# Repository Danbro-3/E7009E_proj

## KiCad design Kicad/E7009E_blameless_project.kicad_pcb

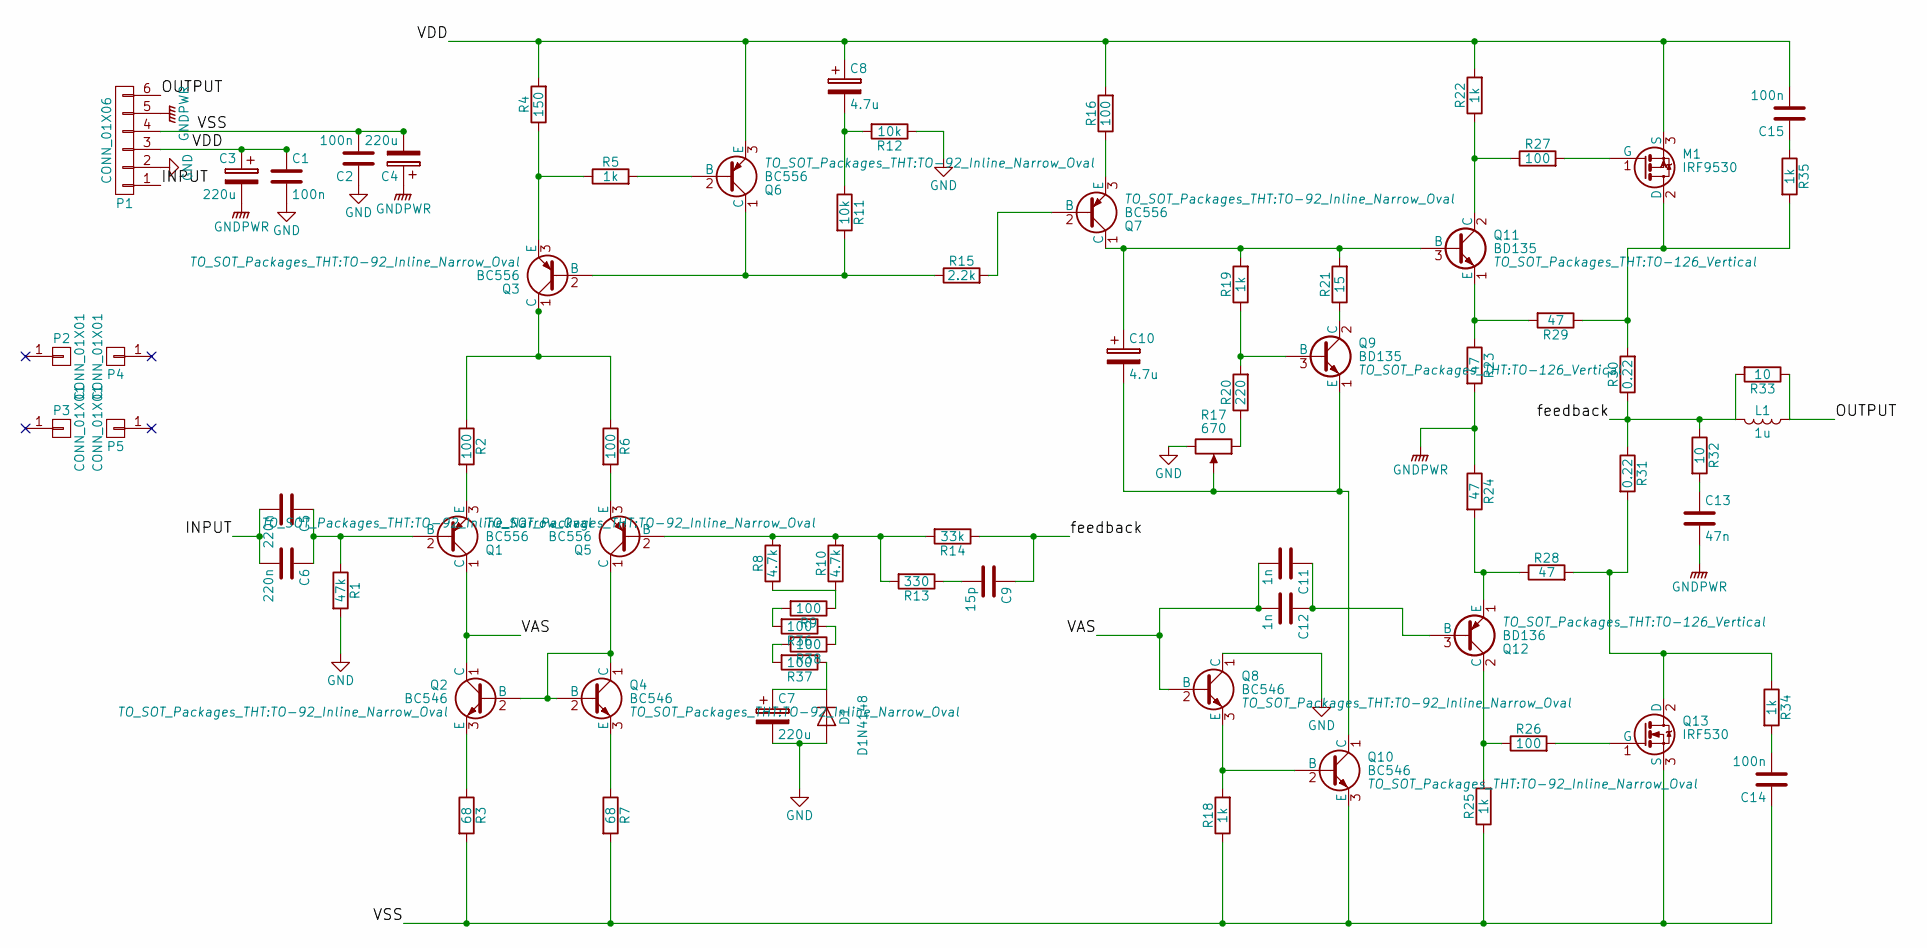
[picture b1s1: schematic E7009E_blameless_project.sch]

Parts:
C1, C2, C14, C15: 100n; C_Disc_D3.0mm_W2.0mm_P2.50mm
C3, C4, C7: 220u; CP_Radial_D8.0mm_P5.00mm
C5, C6: 220n; C_Disc_D3.0mm_W2.0mm_P2.50mm
C8, C10: 4.7u; CP_Radial_D5.0mm_P2.50mm
C9: 15p; C_Disc_D3.0mm_W1.6mm_P2.50mm
C11, C12: 1n; C_Disc_D3.0mm_W1.6mm_P2.50mm
C13: 47n; C_Disc_D3.0mm_W2.0mm_P2.50mm
D1: D1N4148; D_5W_P5.08mm_Vertical_AnodeUp
L1: 1u; Coil_p11mm_L15mm_d10mm
M1: IRF9530; TO-220_Vertical
P1: CONN_01X06; Pin_Header_Straight_1x06_Pitch2.54mm
P2, P3, P4, P5: CONN_01X01; Mounting_D3mm_Pad1mm_totd6mm
Q1, Q3, Q5, Q6, Q7: BC556; TO-92_Inline_Narrow_Oval
Q2, Q4, Q8, Q10: BC546; TO-92_Inline_Narrow_Oval
Q9, Q11: BD135; TO-126_Vertical
Q12: BD136; TO-126_Vertical
Q13: IRF530; TO-220_Vertical
R1: 47k; R_Axial_DIN0204_L3.6mm_D1.6mm_P5.08mm_Horizontal
R2, R6, R9, R16, R26, R27, R36, R37, R38: 100; R_Axial_DIN0204_L3.6mm_D1.6mm_P5.08mm_Horizontal
R3, R7: 68; R_Axial_DIN0204_L3.6mm_D1.6mm_P5.08mm_Horizontal
R4: 150; R_Axial_DIN0204_L3.6mm_D1.6mm_P5.08mm_Horizontal
R5, R18, R19, R22, R25, R34, R35: 1k; R_Axial_DIN0204_L3.6mm_D1.6mm_P5.08mm_Horizontal
R8, R10: 4.7k; R_Axial_DIN0204_L3.6mm_D1.6mm_P5.08mm_Horizontal
R11, R12: 10k; R_Axial_DIN0204_L3.6mm_D1.6mm_P5.08mm_Horizontal
R13: 330; R_Axial_DIN0204_L3.6mm_D1.6mm_P5.08mm_Horizontal
R14: 33k; R_Axial_DIN0204_L3.6mm_D1.6mm_P5.08mm_Horizontal
R15: 2.2k; R_Axial_DIN0204_L3.6mm_D1.6mm_P5.08mm_Horizontal
R17: 670; Potentiometer_Trimmer_Bourns_3296W
R20: 220; R_Axial_DIN0204_L3.6mm_D1.6mm_P5.08mm_Horizontal
R21: 15; R_Axial_DIN0204_L3.6mm_D1.6mm_P5.08mm_Horizontal
R23, R24, R28, R29: 47; R_Axial_DIN0204_L3.6mm_D1.6mm_P5.08mm_Horizontal
R30, R31: 0.22; R_Axial_DIN0207_L6.3mm_D2.5mm_P17.15mm_Horizontal
R32, R33: 10; R_Axial_DIN0414_L11.9mm_D4.5mm_P25.40mm_Horizontal

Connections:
/INPUT: C5.2, C6.2, P1.1
/OUTPUT: L1.1, P1.6, R33.1
/VAS: C11.2, C12.2, Q1.1 (C), Q2.1 (C), Q8.2 (B)
/VDD: C1.1, C3.1, C8.1, C15.2, M1.3 (S), P1.3, Q6.3 (E), R4.2, R16.2, R22.2
/VSS: C2.2, C4.2, C14.1, P1.4, Q10.3 (E), Q13.3 (S), R3.2, R7.2, R18.1, R25.1
/feedback: C9.1, L1.2, R14.1, R30.1, R31.1, R32.1, R33.2
GND: C1.2, C2.1, C7.2, D1.2 (A), P1.2, Q8.1 (C), R1.2, R12.1, R17.3
GNDPWR: C3.2, C4.1, C13.2, P1.5, R23.2, R24.1
unnamed: C5.1, C6.1, Q1.2 (B), R1.1
unnamed: C7.1, D1.1 (K), R37.1
unnamed: C8.2, R11.1, R12.2
unnamed: C9.2, R13.1
unnamed: C10.1, Q7.1 (C), Q11.3 (B), R19.2, R21.2
unnamed: C10.2, Q9.1 (E), Q10.1 (C), R17.2
unnamed: C11.1, C12.1, Q12.3 (B)
unnamed: C13.1, R32.2
unnamed: C14.2, R34.2
unnamed: C15.1, R35.1
unnamed: M1.1 (G), R27.2
unnamed: M1.2 (D), R29.1, R30.2, R35.2
unnamed: Q1.3 (E), R2.2
unnamed: Q2.2 (B), Q4.1 (C), Q4.2 (B), Q5.1 (C)
unnamed: Q2.3 (E), R3.1
unnamed: Q3.1 (C), R2.1, R6.1
unnamed: Q3.2 (B), Q6.1 (C), R11.2, R15.1
unnamed: Q3.3 (E), R4.1, R5.1
unnamed: Q4.3 (E), R7.1
unnamed: Q5.2 (B), R8.2, R10.2, R13.2, R14.2
unnamed: Q5.3 (E), R6.2
unnamed: Q6.2 (B), R5.2
unnamed: Q7.2 (B), R15.2
unnamed: Q7.3 (E), R16.1
unnamed: Q9.2 (C), R21.1
unnamed: Q9.3 (B), R19.1, R20.2
unnamed: Q8.3 (E), Q10.2 (B), R18.2
unnamed: Q11.1 (E), R23.1, R29.2
unnamed: Q11.2 (C), R22.1, R27.1
unnamed: Q12.1 (E), R24.2, R28.1
unnamed: Q12.2 (C), R25.2, R26.1
unnamed: Q13.1 (G), R26.2
unnamed: Q13.2 (D), R28.2, R31.2, R34.1
unnamed: R8.1, R9.1, R10.1
unnamed: R17.1, R20.1
unnamed: R36.1, R38.1
unnamed: R9.2, R36.2
unnamed: R37.2, R38.2

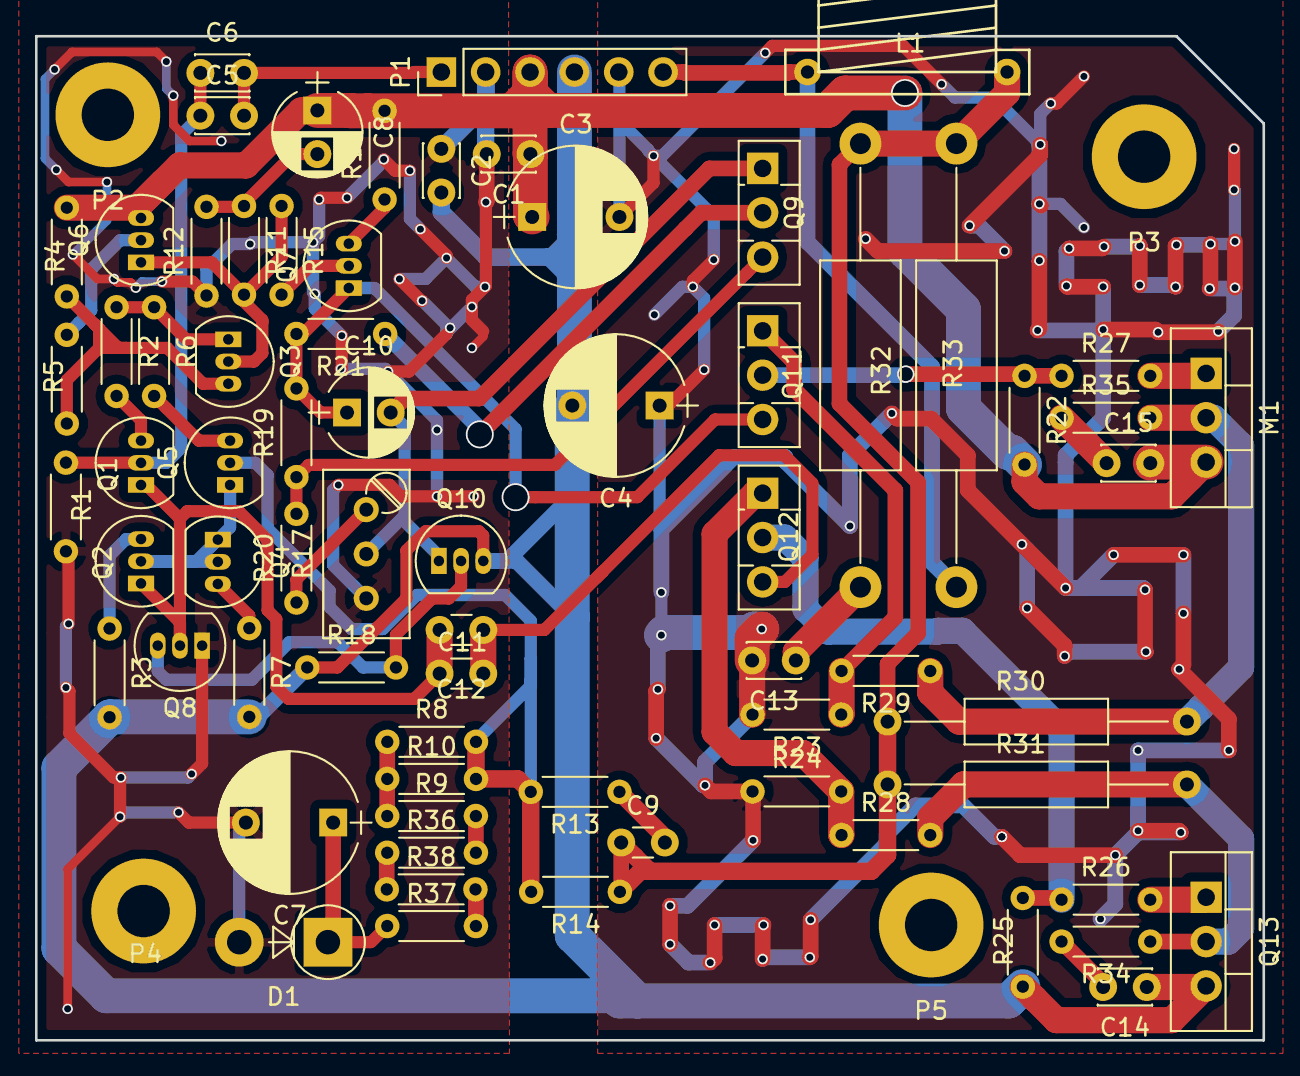
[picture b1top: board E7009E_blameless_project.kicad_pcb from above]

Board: 2 copper layers, 70.3 x 57.5 mm, 74 parts (0 on the bottom side), 46 nets.

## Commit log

2017-09-27 Initiate git
2017-09-28 Added Kicad stuff
2017-09-28 Complete Circuitry and PCB design
2017-11-10 PNG's and stuff
